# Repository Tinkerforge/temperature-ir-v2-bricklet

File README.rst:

Temperature IR Bricklet 2.0
===========================

This repository contains the firmware source code and the hardware design
files. The documentation generator configs can be found at
https://github.com/Tinkerforge/generators

Repository Content
------------------

software/:
 * examples/: Examples for all supported languages
 * build/: Compiled files
 * src/: Source code of firmware
 * Makefile: Makefile to build project

hardware/:
 * Contains KiCad project files and additionally schematics as PDF

datasheets/:
 * Contains datasheets for sensors and complex ICs that are used

Hardware
--------

The hardware is designed with the open source EDA Suite KiCad
(http://www.kicad.org). Before you are able to open the files,
you have to install the Tinkerforge kicad-libraries
(https://github.com/Tinkerforge/kicad-libraries). You can either clone
them directly in hardware/ or clone them in a separate folder and
symlink them into hardware/
(ln -s kicad_path/kicad-libraries project_path/hardware). After that you
can open the .pro file in hardware/ with KiCad and from there view and
modify the schematics and the PCB layout.

Software
--------

If you want to do your own Brick/Bricklet firmware development we highly
recommend that you use our build environment setup script and read the
tutorial (https://www.tinkerforge.com/en/doc/Tutorials/Tutorial_Build_Environment/Tutorial.html).

To compile the C code we recommend you to install the newest GNU Arm Embedded
Toolchain (https://launchpad.net/gcc-arm-embedded/+download).
You also need to install bricklib2 (https://github.com/Tinkerforge/bricklib2).

You can either clone it directly in software/src/ or clone it in a
separate folder and symlink it into software/src/
(ln -s bricklib_path/bricklib2 project_path/software/src/). Finally make sure to
have CMake installed (http://www.cmake.org/cmake/resources/software.html).

After that you can build the firmware by invoking make in software/.
The firmware (.zbin) can then be found in software/build/ and uploaded
with brickv (click button "Flashing" on start screen).

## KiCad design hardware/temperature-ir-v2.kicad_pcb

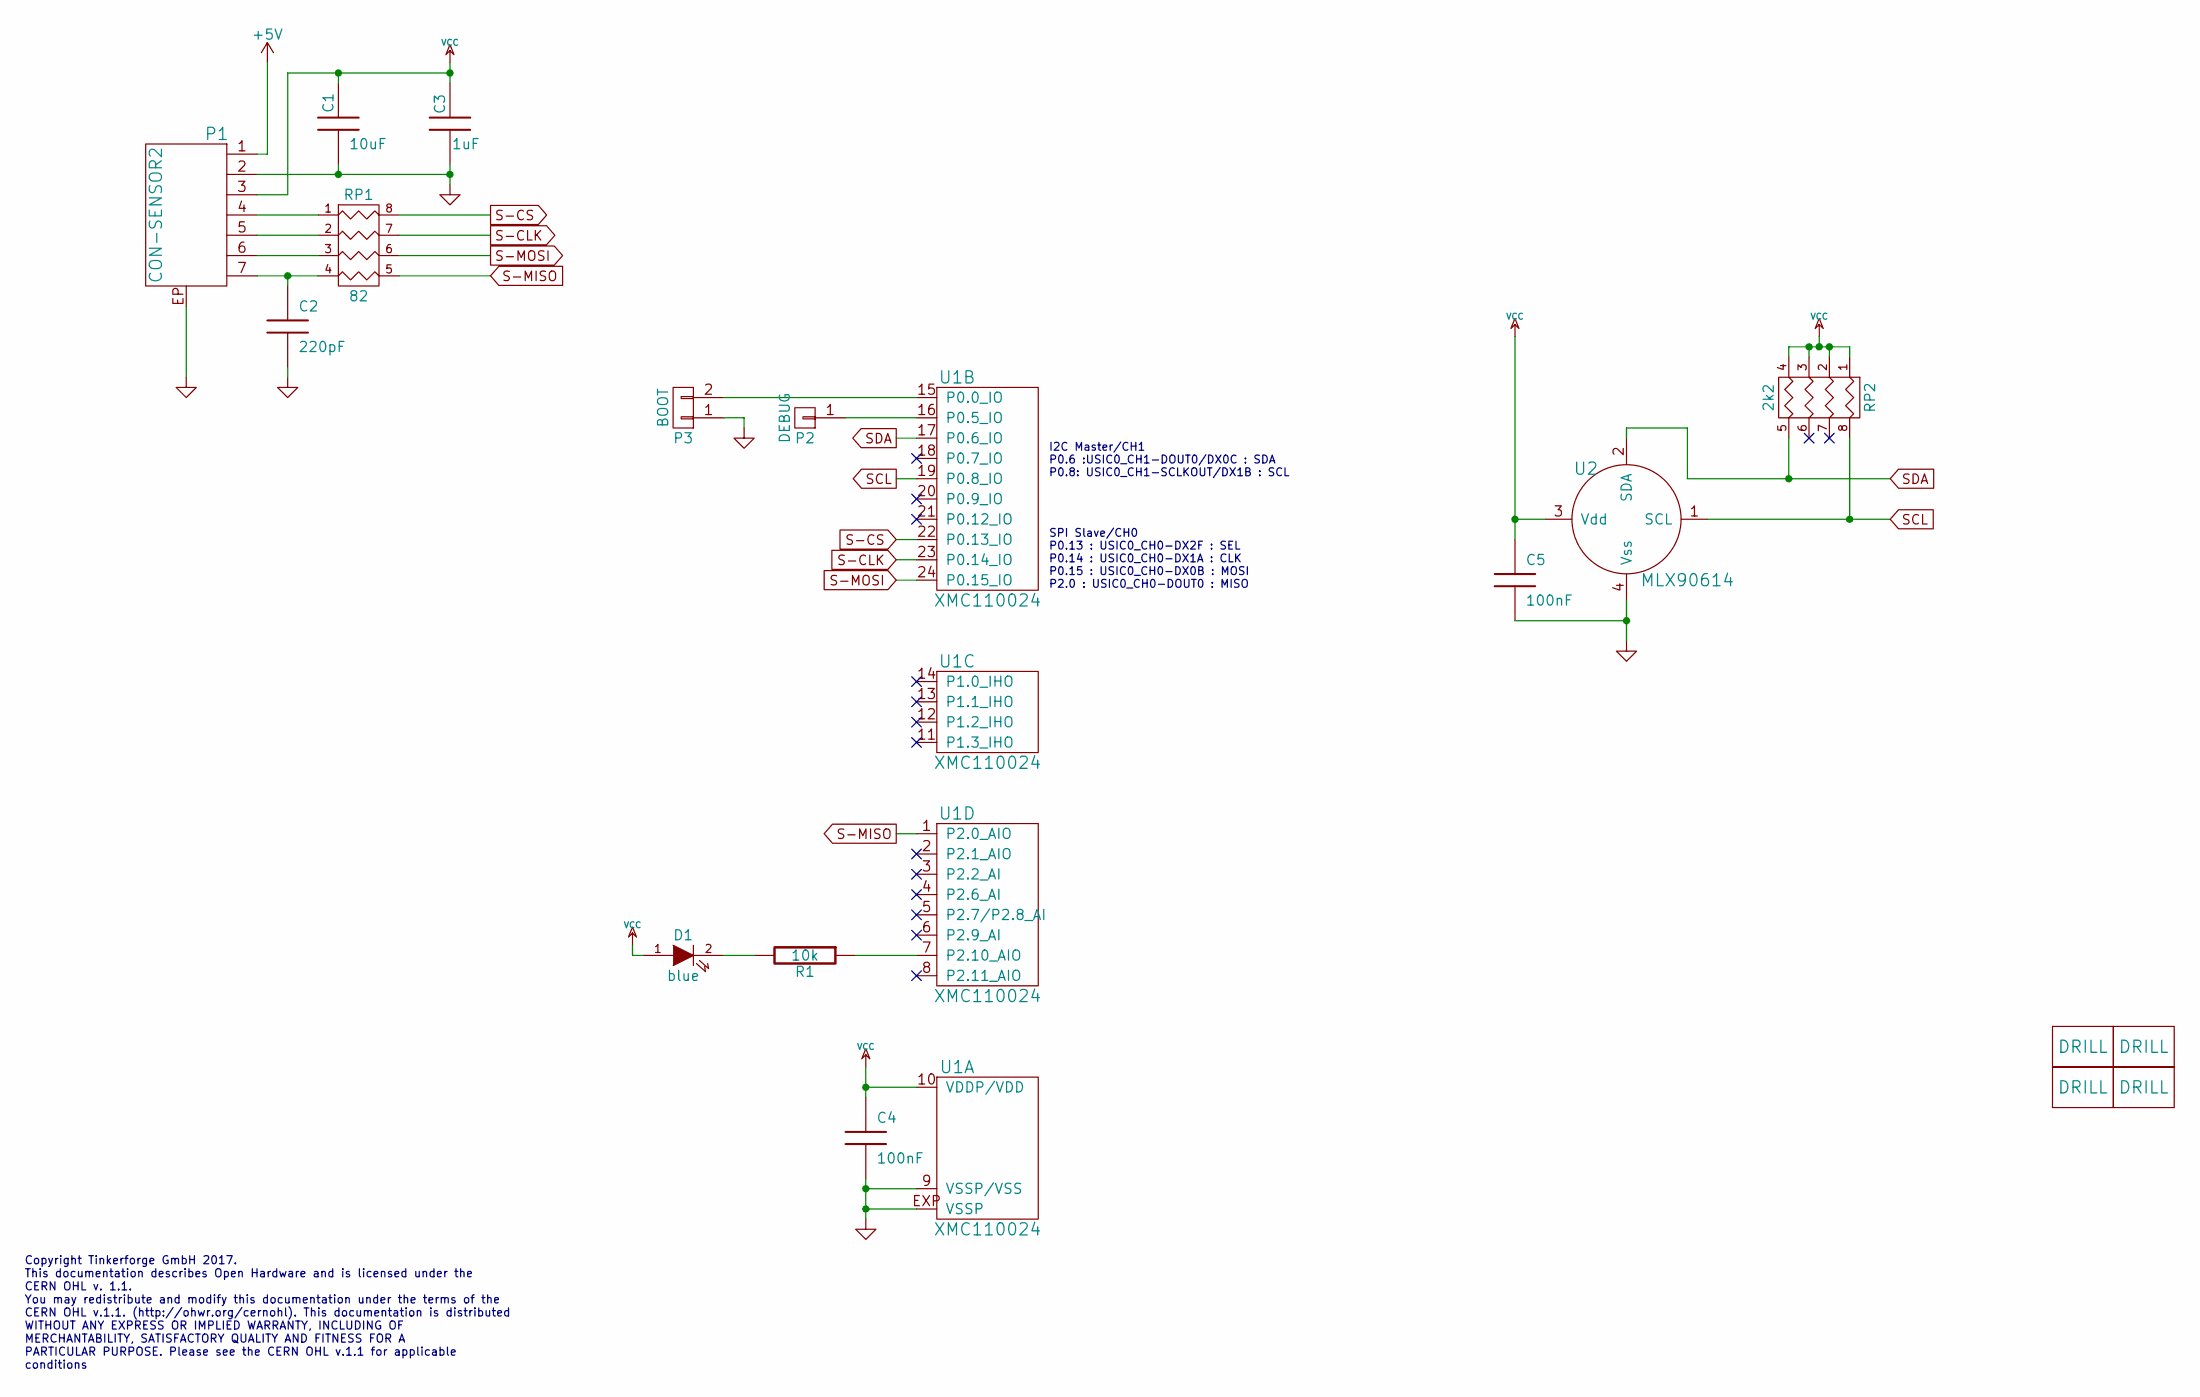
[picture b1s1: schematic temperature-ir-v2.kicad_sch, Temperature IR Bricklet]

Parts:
C1: 10uF; C0805
C2: 220pF; C0402F
C3: 1uF; C0603F
C4, C5: 100nF; C0603F
D1: blue; D0603F
P1: CON-SENSOR2
P2: DEBUG; DEBUG_PAD
P3: BOOT; SolderJumper
R1: 10k; R0603F
RP1: 82; 4X0402
RP2: 2k2; 4X0402
U1: XMC110024; QFN24-4x4mm-0.5mm
U2: MLX90614; TO-39
U4, U5, U6, U7: DRILL; DRILL_NP

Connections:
+5V: P1.1
GND: C1.2, C2.2, C3.1, C4.2, C5.2, P1.2, P1.EP, P3.1, U1.9 (VSSP/VSS), U1.EXP (VSSP), U2.4 (Vss)
unnamed: C2.1, P1.7, RP1.4
unnamed: D1.2 (K), R1.2
unnamed: P1.4, RP1.1
unnamed: P1.5, RP1.2
unnamed: P1.6, RP1.3
unnamed: P2.1, U1.16 (P0.5_IO)
unnamed: P3.2, U1.15 (P0.0_IO)
unnamed: R1.1, U1.7 (P2.10_AIO)
S-CLK: RP1.7 (R2), U1.23 (P0.14_IO)
S-CS: RP1.8 (R1), U1.22 (P0.13_IO)
S-MISO: RP1.5 (R4), U1.1 (P2.0_AIO)
S-MOSI: RP1.6 (R3), U1.24 (P0.15_IO)
SCL: RP2.8 (R1), U1.19 (P0.8_IO), U2.1 (SCL)
SDA: RP2.5 (R4), U1.17 (P0.6_IO), U2.2 (SDA)
VCC: C1.1, C3.2, C4.1, C5.1, D1.1 (A), P1.3, RP2.1, RP2.2, RP2.3, RP2.4, U1.10 (VDDP/VDD), U2.3 (Vdd)

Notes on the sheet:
SPI Slave/CH0 P0.13 : USIC0_CH0-DX2F : SEL P0.14 : USIC0_CH0-DX1A : CLK P0.15 : USIC0_CH0-DX0B : MOSI P2.0 : USIC0_CH0-DOUT0 : MISO
I2C Master/CH1 P0.6 :USIC0_CH1-DOUT0/DX0C : SDA P0.8: USIC0_CH1-SCLKOUT/DX1B : SCL
Copyright Tinkerforge GmbH 2017. This documentation describes Open Hardware and is licensed under the CERN OHL v. 1.1. You may redistribute and modify this documentation under the terms of the CERN OHL v.1.1. (http://ohwr.org/cernohl). This documentation is distributed WITHOUT ANY EXPRESS OR IMPLIE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

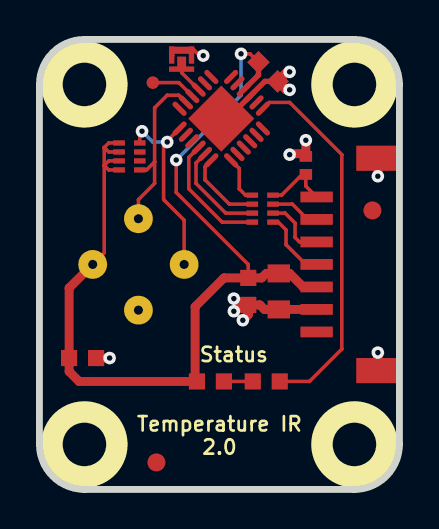
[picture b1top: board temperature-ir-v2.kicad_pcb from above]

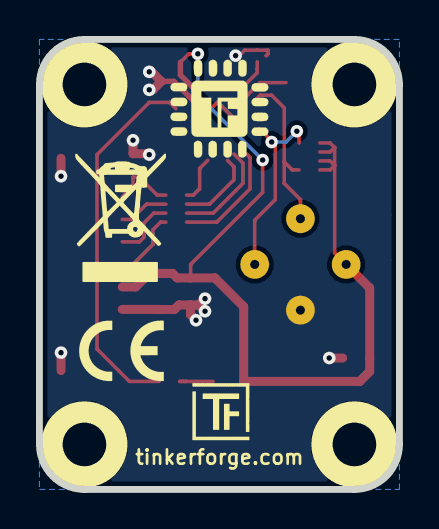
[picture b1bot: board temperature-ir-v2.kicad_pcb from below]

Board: 2 copper layers, 20.0 x 25.0 mm, 23 parts (3 on the bottom side), 16 nets.

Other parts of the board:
Fiducial_Mark: VAL**; Fiducial_Mark
Fiducial_Mark#2: VAL**; Fiducial_Mark
Ref**: Val**; Logo_31x31
VAL: WEEE_7mm
VAL#2: CE_5mm

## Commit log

2017-09-14 Add license and datasheet
2017-09-14 Add schematic
2017-09-14 Change footprints
2017-09-14 Add PCB
2017-09-14 Place CE & WEEE logo
2017-09-14 Add missing GND via, fix BootPad
2017-09-18 Add CoMCU Logo
2017-09-22 Add initial version of firmware
    The workflow is mostly copied from the old Temperature IR Bricklet,
    so this should work in priciple.
    This code is however not yet tested at all (prototype did not arrive yet).
2017-09-28 turn logging off
2017-09-28 Remove TODO, 20kHz is OK
2017-09-28 Fix I2C address
2017-09-28 Check for checksum correctly
2017-09-28 Initialize MLX struct with 0s
2017-09-28 Handle 0 emissivity
2017-09-28 Use timer to make sure we only read every 50ms
2017-09-28 Add timer variable
2017-09-28 Move idle state to if case after switch
2017-10-18 move sensor to the center
2017-10-19 fix status led text
2017-10-23 Add 3d model (*.step & *.FCStd)
2017-10-26 specify processor type
2017-12-07 Add examples
2018-02-01 Fix path of the 3d model of the IR sensor
2018-02-02 Update examples
2018-02-16 Update 3d model
2018-02-16 Add schematic (PDF)
2018-02-19 add cutout description
2018-02-19 javascript: Close div tag correctly
2018-02-20 Cleanup KiCad libraries config
    Ensure LibDir=kicad-libraries and LibName1=tinkerforge.
    Remove special library.
2018-03-05 Remove unused flash-size define
2018-05-11 Rename files
2018-05-24 perl: Use strict in examples
2018-06-06 Adapt to bricklib2 callback-value changes to fix wrong length of get-object/ambient-temperature packets
2018-06-06 Update changelog and version
2018-06-06 Add LabVIEW examples
2018-06-07 Add date ref for version 2.0.1 to changelog
2018-06-18 Change capacitor footprint(s) to C0402F
2018-06-28 Fix readme
2018-07-11 Add Makefile with docker support
2018-07-11 Remove obsolete generate_makefile scripts
2018-07-11 Update directory structure and build instructions
2018-09-14 vbnet: Fix typo in comment
2018-10-04 Increase version for new release (changes in bricklib2)
2018-10-04 Add rev to changelog
2018-11-06 Add rust examples
2018-11-07 rust: Accept host names for ip connection, fix naming inconsistencies
2018-11-07 rust: Rename callback receivers.
2018-12-14 Add go examples.
2018-12-14 go: Fix printf parameters.
2018-12-18 go: Change import path.
2018-12-18 go: Change import path again.
2018-12-20 rust: Reformat examples.
2019-01-24 mqtt: Add examples.
2019-01-24 mqtt: Fix example header.
2019-01-24 mqtt: Remove executable bit in example permissions.
2019-01-24 go: Minor example fixes.
2019-01-24 mqtt: Minor example fixes.
2019-02-19 fix libraries
2019-02-19 Use release version boot and debug pins
2019-02-19 Use coop task instead of state machine and add error handling
    We use the newly introduced coop task to make the handing of different
    states easier. Additionally we handle errors that may occur after
    changing the emissivity.
    Changing the emissivity now has proper wait times (Between erase and
    write).
    If we get 5 errors in a row, we reset the MLX90614 by gooing to sleep,
2019-02-19 Add changelog for 2.0.3
2019-02-19 Add rev for 2.0.3
2019-03-28 mqtt: Fix whitespace.
2019-05-09 fix status text
2019-05-09 move product text
2019-08-22 c: Adapt to bindings changes
2020-01-13 examples: Use python3 input instead of python2 raw_input.
2020-01-13 examples: mqtt: Remove trailing whitespace.
2020-03-16 Whitespace
2020-04-07 examples: rust: Always block when calling bindings functions.
2020-08-19 Add uc examples.
2020-08-25 uc: Fix whitespace
2020-08-27 uc: Fix warnings.
2020-09-02 uc: Add example driver note.
2020-10-16 uc: Fix divisor type.
2021-10-25 Update KiCad link
    https://www.kicad.org/blog/2021/10/Avoid-links-to-former-kicad-domain/
2022-04-19 examples: uc: Rename TF_HalContext to TF_HAL.
2022-04-27 uc: Adapt to bindings changes
2022-07-06 Add license files.
2023-06-21 move to new kicad version
2025-10-04 Fix compatibility with new Docker build image (GCC 14.2.1)

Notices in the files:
hardware/temperature-ir-v2.kicad_pcb:
Licensed under CERN OHL v.1.1
Copyright (©) 2017, B.Nordmeyer
